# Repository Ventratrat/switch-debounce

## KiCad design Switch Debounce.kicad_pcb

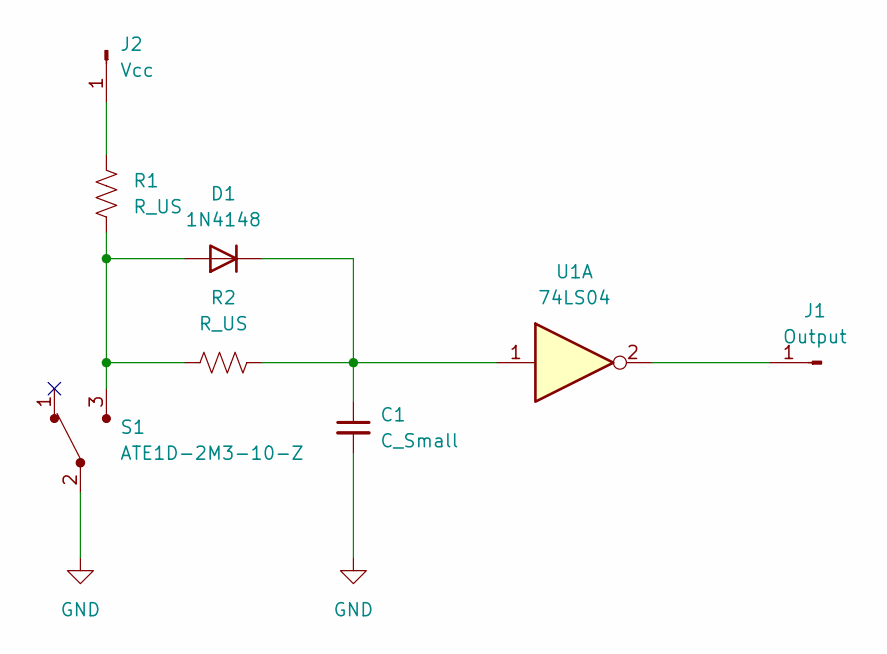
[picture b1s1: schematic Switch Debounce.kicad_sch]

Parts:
C1: C_Small; Capacitor_4mm_diam_.6mm_pin
D1: 1N4148; D_DO-35_SOD27_P7.62mm_Horizontal
J1: Output; Wire Hole
J2: Vcc; Wire Hole
R1, R2: R_US; R_1watt
S1: ATE1D-2M3-10-Z; Switch_Toggle_ATE1D-2M3-10-Z; MPN ATE1D-2M3-10-Z; Digi-Key_PN 563-1157-ND
U1: 74LS04; DIP-14_W7.62mm

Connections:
GND: C1.2, S1.2 (Com), U1.7 (GND)
unnamed: D1.2 (A), R1.2, R2.1, S1.3
unnamed: C1.1, D1.1 (K), R2.2, U1.1
unnamed: J1.1, U1.2
unnamed: J2.1, R1.1, U1.14 (VCC)

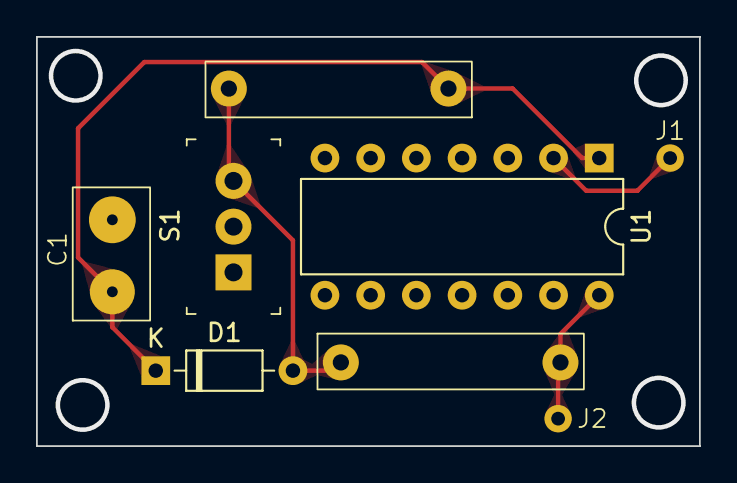
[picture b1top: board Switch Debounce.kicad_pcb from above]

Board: 2 copper layers, 36.8 x 22.7 mm, 8 parts (0 on the bottom side), 5 nets.

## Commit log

2024-03-25 Added project files
